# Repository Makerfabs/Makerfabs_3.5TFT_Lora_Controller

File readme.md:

# Makerfas 3.5“ TFT Lora Controller

```c++
/*
Version:		V1.2
Author:			Vincent
Create Date:	2021/9/18
Note:
		V1.1 Add more description.
		V1.2 Add wiki and shop link. Add Lora Kit firmware.
*/
```

[toc]

# Makerfabs

[Makerfabs home page](https://www.makerfabs.com/)

[Makerfabs Wiki](https://wiki.makerfabs.com/)

# Lora Radio Expansion

## Intruduce

Product Link ：[Lora-radio-expansion-for-esp32-display](https://www.makerfabs.com/lora-radio-expansion-for-esp32-display.html)

Wiki Link :  [LoRa_Radio_Expansion](https://wiki.makerfabs.com/MaTouch_3.5_TFT_Touch_with_Camera.html#use-with-lora-radio-expansion)

LoRa Radio expansion based on the LoRa module and provided a wireless Lot solution (ESP32-LoRa). This board is designed for ESP32 3.5" TFT Touch with Camera (also for the 3.2" one), mainly used with the ESP32 3.5" TFT Touch board.

We used LoRa Radio expansion and  ESP32 3.5" TFT Touch with Camera to make a Lora control terminal, which can control multiple Lora devices at the same time through the touch screen and display the device status in real time.

It is an extension of Touch Screen Camera series.

[ESP32 TFT LCD with Camera(3.5'')](https://wiki.makerfabs.com/MaTouch_3.5_TFT_Touch_with_Camera.html))

[ESP32 TFT LCD with Camera(3.2'')](https://wiki.makerfabs.com/MaTouch_3.2_TFT_LCD_with_Camera.html))

## Feature

- Onboard LoRa module (433Mhz, 868Mhz or 915Mhz)
- Long communication distance: 2km or more
- Active buzzer
- Power by 3.3V

### Front:

### Back:

# Makerfas 3.5“ TFT Lora Controller

**Disclaimer, this is only a demo, not as a hardware product for sale, only for reference.**

## Introduce

[ESP32 TFT LCD with Camera(3.5'')](https://wiki.makerfabs.com/MaTouch_3.5_TFT_Touch_with_Camera.html)) was used as a demonstration.

An open Lora control terminal that currently supports 6 Makerfabs of Lora nodes (some are not for sale).  Realizes UI interface, can increase sensor according to UID. And there are different control interfaces for different nodes. 

Five nodes can be online at the same time and the node status is updated periodically. 

## How to use

We're going to post a video to show you how to do that.

### Main page

The main page allows you to add nodes, clear all nodes, and enter receive mode.

The status of each logged node can be updated periodically.

And you can click the node button to enter the node interface.

### Node Page

In node page, you can view the node type, UID, and icon.

You can also refresh the node status periodically.

### Node Control Page

Some types of nodes have control functions, such as controlling the Relay switch and the size of AC Dimmer.

Click the button to enter the keypad or change the switch state.

## Code Upload

Firmware is in .\firmware\ESP32TFT3.5-LORA

### Compiler Options

**If you have any questions，such as how to install the development board, how to download the code, how to install the library. Please refer to :[Makerfabs_FAQ](https://github.com/Makerfabs/Makerfabs_FAQ)**

- Install board : ESP32 (Version 1.0.6)

- Install library: LovyanGFX, RadioLib(Version 4.6.0)

- Copy all bmp file to TF cards and insert to esp32
- Upload codes, select "ESP32 Wrover Module" and "Huge APP"

*Use other version board or library maybe not be able to complied.*

### Change Lora Frequency

Makerfas 3.5“ TFT Lora Controller main code. The default Lora frequency is 434 MHz, you can change these codes:

```c++
//In .\firmware\ESP32TFT3.5-LORA\makerfabs_pin.h

#define FREQUENCY 434.0
#define BANDWIDTH 125.0
#define SPREADING_FACTOR 9
#define CODING_RATE 7
#define OUTPUT_POWER 10
#define PREAMBLE_LEN 8
#define GAIN 0
```

# Example Nodes

We removed the relevant Lora Nodes demo.
Now all based on the example of "328p + lora" has moved to the [Makerfabs_MaLora]( ()https://github.com/Makerfabs/Makerfabs_MaLora) in the project.

# Lora Soil Monitoring & Irrigation Kit

## Introduce

This Kit is based on ESP32 and Lora. The ESP32 3.5 inch display is the console for the system, it receives the Lora message from Lora moisture sensors (support up to 8 sensors in our default firmware) , and send control commands to Lora 4-chnanel MOSFET(2 4-channel MOSFET supported, with totally 8 channels), to control the connected valves open/close, and thus to control the irrigation for multiple points.

Shop Link: [Lora Soil Monitoring & Irrigation Kit](https://www.makerfabs.com/lora-soil-monitoring-irrigation-kit.html)

Please refer to instructables for instructions:

Instructables Link: [Soil-Monitoring-and-Irrigation-With-Lora](https://www.instructables.com/Soil-Monitoring-and-Irrigation-With-Lora/)

Youtube Link: [Soil Monitoring and Irrigation with Lora - How it Works](https://www.youtube.com/watch?v=p6YZIw9I9zE&feature=emb_imp_woyt)

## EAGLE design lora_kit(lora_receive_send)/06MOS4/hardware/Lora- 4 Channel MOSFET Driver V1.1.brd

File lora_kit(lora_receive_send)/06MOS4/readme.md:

Makerfabs Lora Node：Lora- 4 Channel MOSFET Driver
 ==

```
/*
Version:		V1.2
Author:			Vincent
Create Date:	2022/3/24
Note:
				2022/4/2	V1.2: Change feature describes.
				2022/4/2	V1.1: Fix readme bug, fix code pin
*/
```

[toc]

# Makerfabs

[Makerfabs home page](https://www.makerfabs.com/)

[Makerfabs Wiki](https://makerfabs.com/wiki/index.php?title=Main_Page)

# Introduce

4-Channel Lora MOSFET based on the Arduino, users can program it with Arduino IDE, which is very easy especially suit for the none-programmers. There are also guide for users to learn how to create the first IoT project with this board, with which the starters can learn the hardware and programming skill quickly. 

Product Link ：[Lora - 4 Channel MOSFET Driver](https://www.makerfabs.com/index.php?route=journal2/quickview&pid=725)

Wiki Link : 

## Feature

* ATMEL Atmega328P: High Performance, Low Power Atmel®AVR® 8-Bit Microcontroller
* Speed Grade:20Mhz
* Flash:32Kbytes
* RAM: 2KBytes
* EEPROM: 1Kbytes
* Maximum current: 2A
* Input Voltage: 5~27V DC
* Onboard opticalcoupler*4

### Front

 ## Pin OUT

Control relay pins: 

| Atmega328P | MOS  |
| ---------- | ---- |
| D5         | K1   |
| D6         | K2   |
| D9         | K3   |
| D3         | K4   |

# Command

## Lora Node Massage

```c
Type ID: 06
Short name: MOS4
```

## Action

| ACT  | PARAM             | Description          |
| ---- | ----------------- | -------------------- |
| 114  | 000000(not parse) | Querying node status |
| 000  | 000000(not parse) | Close all MOS        |
| 001  | 000000(not parse) | Open all MOS         |
| 002  | 00XXXX            | Set 4 channel MOS    |

### ACT 002

The last four digits of PARAM represent the states of the four MOS.  

The status ranges from 0 to 8:

| Status | 0    | 1     | 2    | 3     | 4    | 5     | 6    | 7     | 8    |
| ------ | ---- | ----- | ---- | ----- | ---- | ----- | ---- | ----- | ---- |
| Power  | 0%   | 12.5% | 25%  | 37.5% | 50%  | 62.5% | 75%  | 87.5% | 100% |

Command example:

```c
ACT = 000 Close
	ID060000ACT000PARAM000000
	//Close all mosfet

ACT = 001 All Open
	ID060000ACT001PARAM000000
	//Open all mosfet, 100% power
    
ACT = 002 Control 
	PARAM = 0000-8888 MOS Status	0,1/8,...,7/8,1
	ID060000ACT002PARAM008010
    //Set mos0 100%; mos1 0%; mos2 12.5%;mos3 0%
```

## Reply

The reply format is as follows:

```c
ID06XXXX[space]REPLY[space]:[space]MOS4[space][Mosfet Status]
    
ID060001 REPLY : MOS4 0801
```

Spaces cannot be omitted.

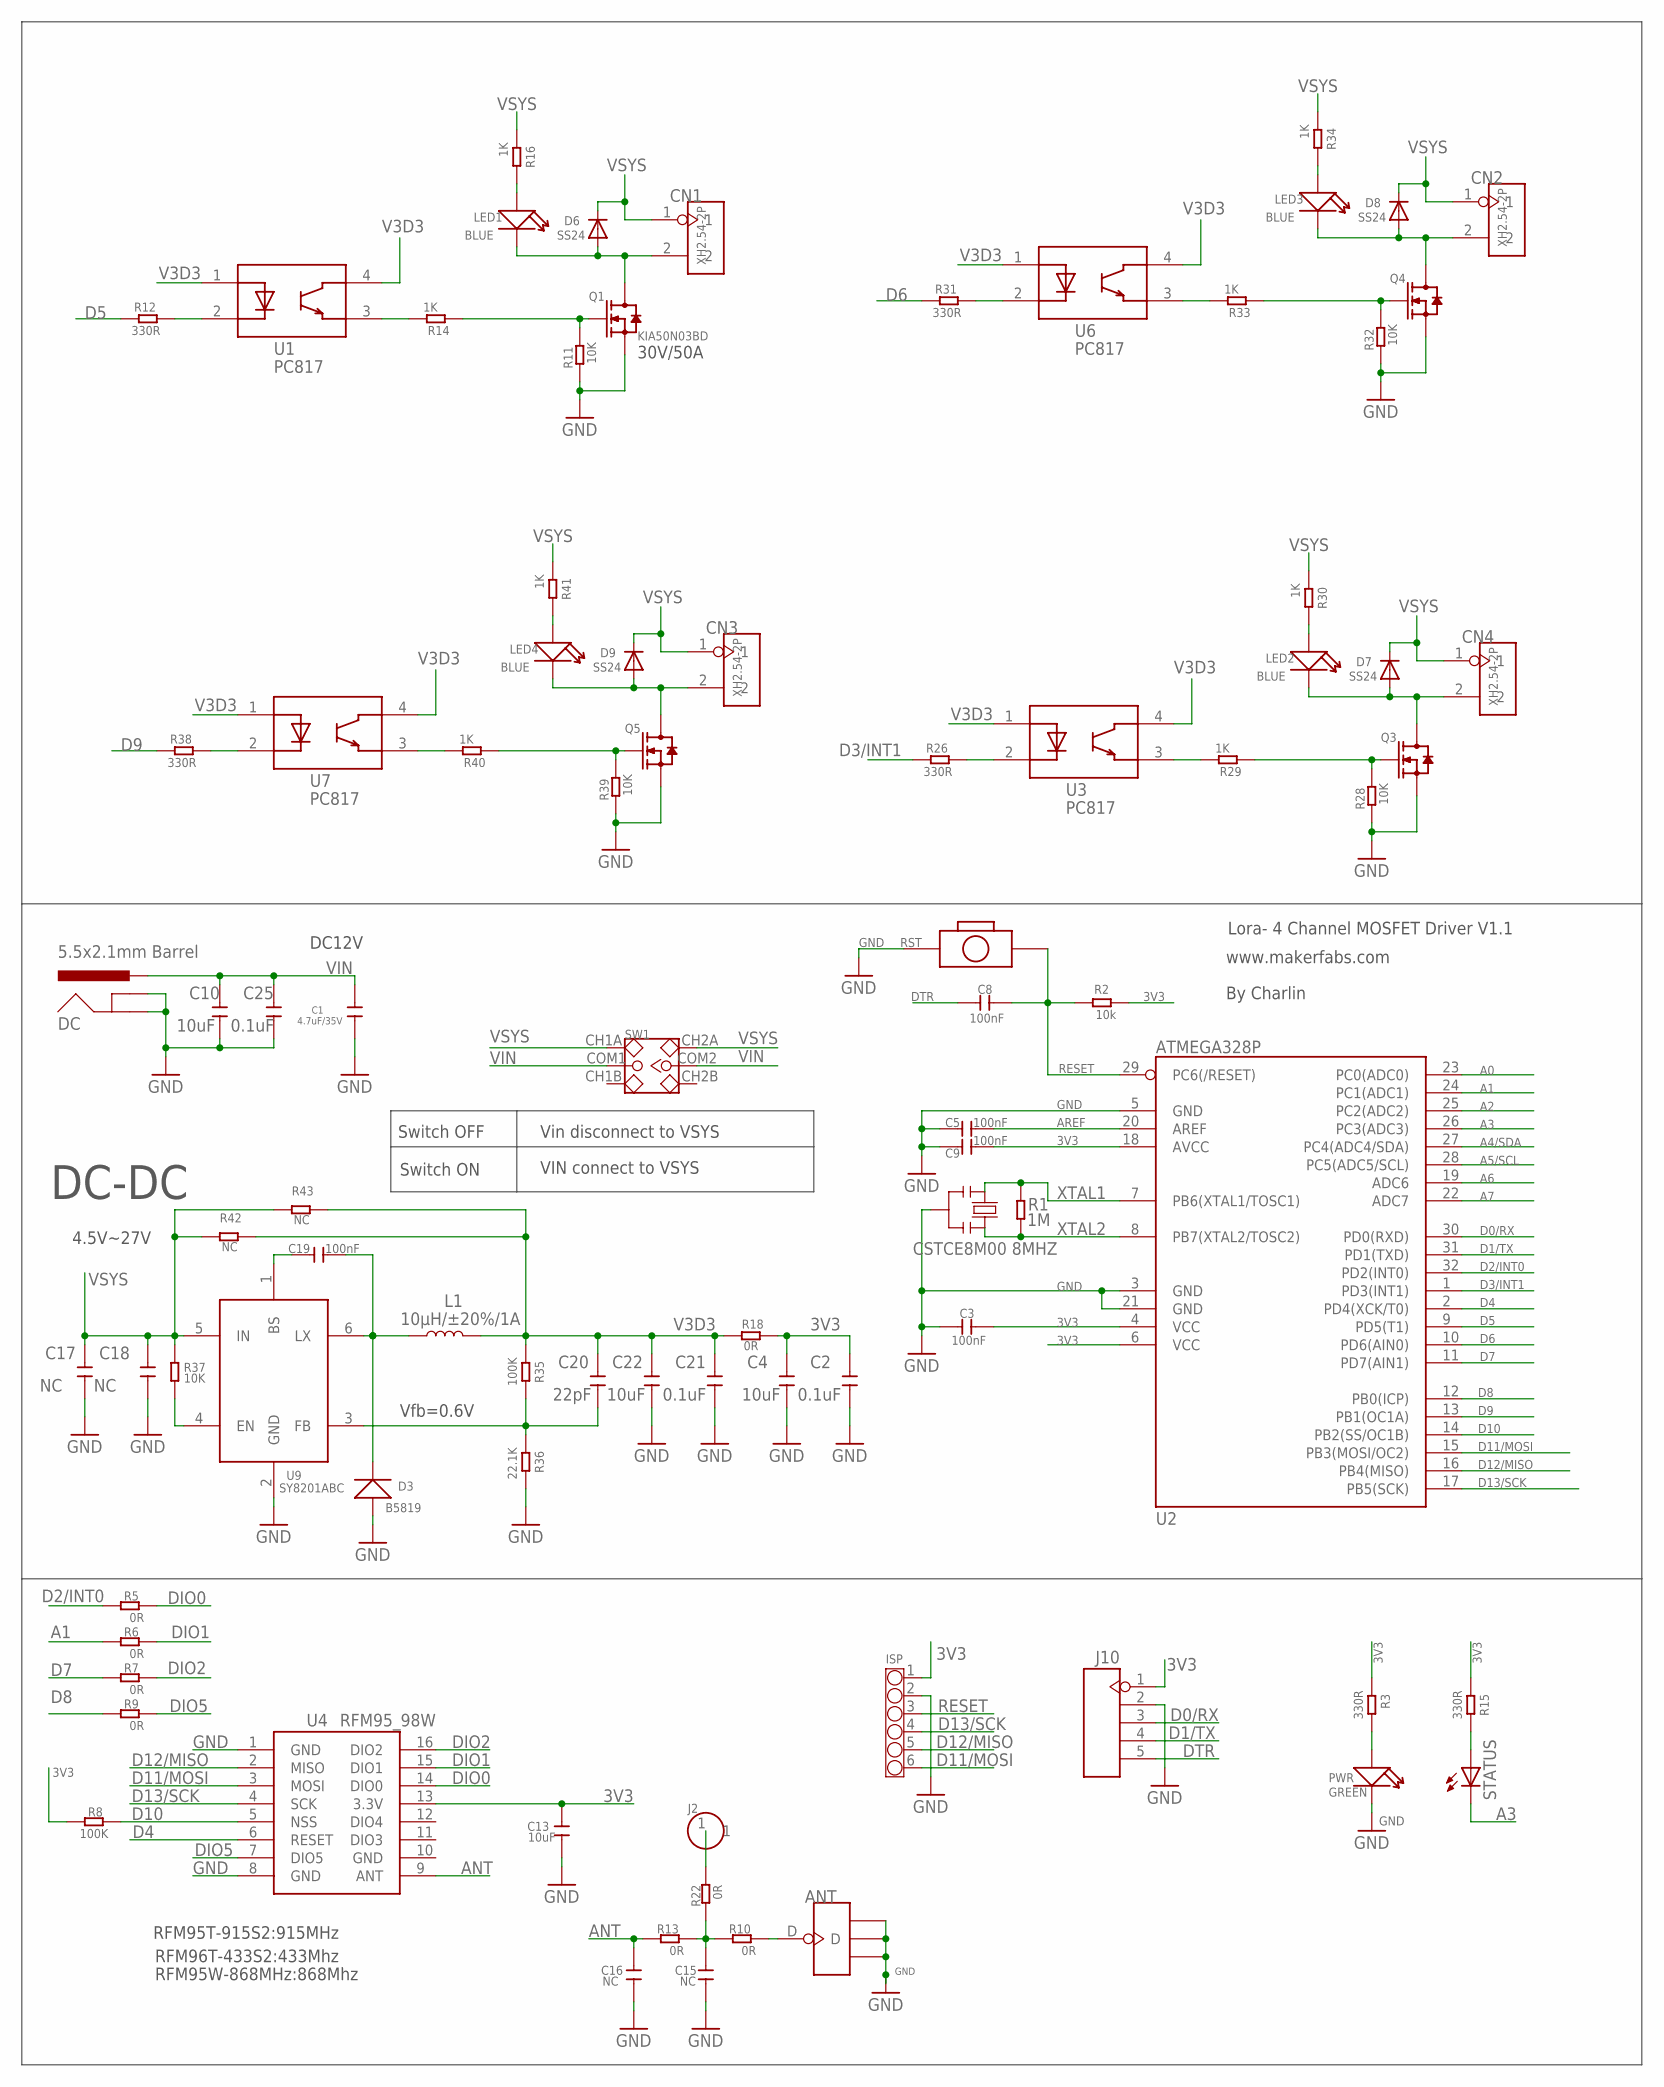
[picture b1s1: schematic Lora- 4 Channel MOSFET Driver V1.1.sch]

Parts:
ANT: ANTENNA-U-FL; 4P-U-FL
C1: 4.7uF/35V; 0603
C2, C21, C25: 0.1uF; 0603
C3, C5, C8, C9, C19: 100nF; 0603
C4, C10, C13, C22: 10uF; 0603
C15, C16, C17, C18: NC; 0603
C20: 22pF; 0603
CN1, CN2, CN3, CN4: XH2.54-2P
D3: B5819; SOD123
D6, D7, D8, D9: SS24; SMADIODE
DC: 5.5x2.1mm Barrel; POWER_JACK_SMD
ISP: CONNECTOR-HEADER-6P-3460270P1; 1X6P-2.54-8.5-BLACK-FEMALE
J2: HEADER-1P-50; 1P-100/50MIL
J10: HEADER-5P-2.54; 5P-2.54
L1: 10µH/±20%/1A; SRN6045
LED1, LED2, LED3, LED4: BLUE; LED-0603
PWR: GREEN; LED-0603
Q1: KIA50N03BD; DISCRETE_TO252
Q3, Q4, Q5: DISCRETE_MOSFET-NP3055LDG; DISCRETE_TO252
R1: 1M; R0603
R2: 10k; R0603
R3, R12, R15, R26, R31, R38: 330R; R0603
R5, R6, R7, R9, R10, R13, R18, R22: 0R; R0603
R8, R35: 100K; R0603
R11, R28, R32, R37, R39: 10K; R0603
R14, R16, R29, R30, R33, R34, R40, R41: 1K; R0603
R36: 22.1K; R0603
R42, R43: NC; R0603
RST: BOTTON-2P-90D; 2P-7.62X3.56-90D
STATUS: LED5MM
SW1: SWITCH-2CH-6P; 6P-2CH-2.54-7.6X3.0
U1, U3, U6, U7: PC817; SMD4-254P-1016L460W
U2: ATMEGA328P; TQFP32
U4: RFM95_98W; RFM92_93W
U9: SY8201ABC; SOT-23-6
Y1: CSTCE8M00 8MHZ; RESONATOR

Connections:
3V3: C2.2, C3.2, C4.2, C9.2, C13.2, ISP.1, J10.1, R2.1, R3.1, R8.2, R15.1, R18.2, U2.4 (VCC), U2.6 (VCC), U2.18 (AVCC), U4.13 (3.3V)
A0: U2.23 (PC0(ADC0))
A1: R6.1, U2.24 (PC1(ADC1))
A2: U2.25 (PC2(ADC2))
A3: STATUS.K (C), U2.26 (PC3(ADC3))
A4/SDA: U2.27 (PC4(ADC4/SDA))
A5/SCL: U2.28 (PC5(ADC5/SCL))
A6: U2.19 (ADC6)
A7: U2.22 (ADC7)
ANT: C16.2, R13.2, U4.9 (ANT)
AREF: C5.2, U2.20 (AREF)
D0/RX: J10.3, U2.30 (PD0(RXD))
D1/TX: J10.4, U2.31 (PD1(TXD))
D2/INT0: R5.1, U2.32 (PD2(INT0))
D3/INT1: R26.1, U2.1 (PD3(INT1))
D4: U2.2 (PD4(XCK/T0)), U4.6 (RESET)
D5: R12.1, U2.9 (PD5(T1))
D6: R31.1, U2.10 (PD6(AIN0))
D7: R7.1, U2.11 (PD7(AIN1))
D8: R9.1, U2.12 (PB0(ICP))
D9: R38.1, U2.13 (PB1(OC1A))
D10: R8.1, U2.14 (PB2(SS/OC1B)), U4.5 (NSS)
D11/MOSI: ISP.6, U2.15 (PB3(MOSI/OC2)), U4.3 (MOSI)
D12/MISO: ISP.5, U2.16 (PB4(MISO)), U4.2 (MISO)
D13/SCK: ISP.4, U2.17 (PB5(SCK)), U4.4 (SCK)
DIO0: R5.2, U4.14 (DIO0)
DIO1: R6.2, U4.15 (DIO1)
DIO2: R7.2, U4.16 (DIO2)
DIO5: R9.2, U4.7 (DIO5)
DTR: C8.1, J10.5
GND: ANT.GND1, ANT.GND2, ANT.GND3, C1.2, C2.1, C3.1, C4.1, C5.1, C9.1, C10.1, C13.1, C15.1, C16.1, C17.1, C18.1, C21.1, C22.1, C25.1, D3.+, DC.GND (GNDBREAK), DC.P$4 (GND), ISP.2, J10.2, PWR.-, Q1.3 (S), Q3.3 (S), Q4.3 (S), Q5.3 (S), R11.1, R28.1, R32.1, R36.2, R39.1, RST.P$1 (1), U2.3 (GND), U2.5 (GND), U2.21 (GND), U4.1 (GND), U4.8 (GND), U4.10 (GND), U9.2 (GND), Y1.2
unnamed: ANT.D, R10.1
unnamed: R12.2, U1.2
unnamed: C15.2, R10.2, R13.1, R22.2
unnamed: R15.2, STATUS.A
unnamed: Q1.1 (G), R11.2, R14.1
unnamed: PWR.+, R3.2
unnamed: J2.1, R22.1
unnamed: CN1.2, D6.A, LED1.-, Q1.2 (D)
unnamed: R14.2, U1.3
unnamed: R26.2, U3.2
unnamed: Q3.1 (G), R28.2, R29.1
unnamed: LED1.+, R16.2
unnamed: R29.2, U3.3
unnamed: CN4.2, D7.A, LED2.-, Q3.2 (D)
unnamed: LED2.+, R30.2
unnamed: R31.2, U6.2
unnamed: C19.2, D3.-, L1.1, U9.6 (LX)
unnamed: C19.1, U9.1 (BS)
unnamed: C20.1, R35.2, R36.1, U9.3 (FB)
unnamed: Q4.1 (G), R32.2, R33.1
unnamed: R33.2, U6.3
unnamed: CN2.2, D8.A, LED3.-, Q4.2 (D)
unnamed: LED3.+, R34.2
unnamed: R38.2, U7.2
unnamed: Q5.1 (G), R39.2, R40.1
unnamed: R40.2, U7.3
unnamed: CN3.2, D9.A, LED4.-, Q5.2 (D)
unnamed: LED4.+, R41.2
unnamed: R37.2, U9.4 (EN)
RESET: C8.2, ISP.3, R2.2, RST.P$2 (2), U2.29 (PC6(/RESET))
V3D3: C20.2, C21.2, C22.2, L1.2, R18.1, R35.1, R42.2, R43.2, U1.1, U1.4, U3.1, U3.4, U6.1, U6.4, U7.1, U7.4
VIN: C1.1, C10.2, C25.2, DC.VIN0 (PWR), SW1.COM1, SW1.COM2
VSYS: C17.2, C18.2, CN1.1, CN2.1, CN3.1, CN4.1, D6.C, D7.C, D8.C, D9.C, R16.1, R30.1, R34.1, R37.1, R41.1, R42.1, R43.1, SW1.CH1A, SW1.CH2A, U9.5 (IN)
XTAL1: R1.2, U2.7 (PB6(XTAL1/TOSC1)), Y1.1
XTAL2: R1.1, U2.8 (PB7(XTAL2/TOSC2)), Y1.3

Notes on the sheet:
RFM95T-915S2:915MHz
RFM96T-433S2:433Mhz
RFM95W-868MHz:868Mhz
Lora- 4 Channel MOSFET Driver V1.1
DC-DC
Switch OFF
Switch ON
Vin disconnect to VSYS
VIN connect to VSYS
DC12V
Vfb=0.6V
4.5V~27V
30V/50A
www.makerfabs.com
By Charlin

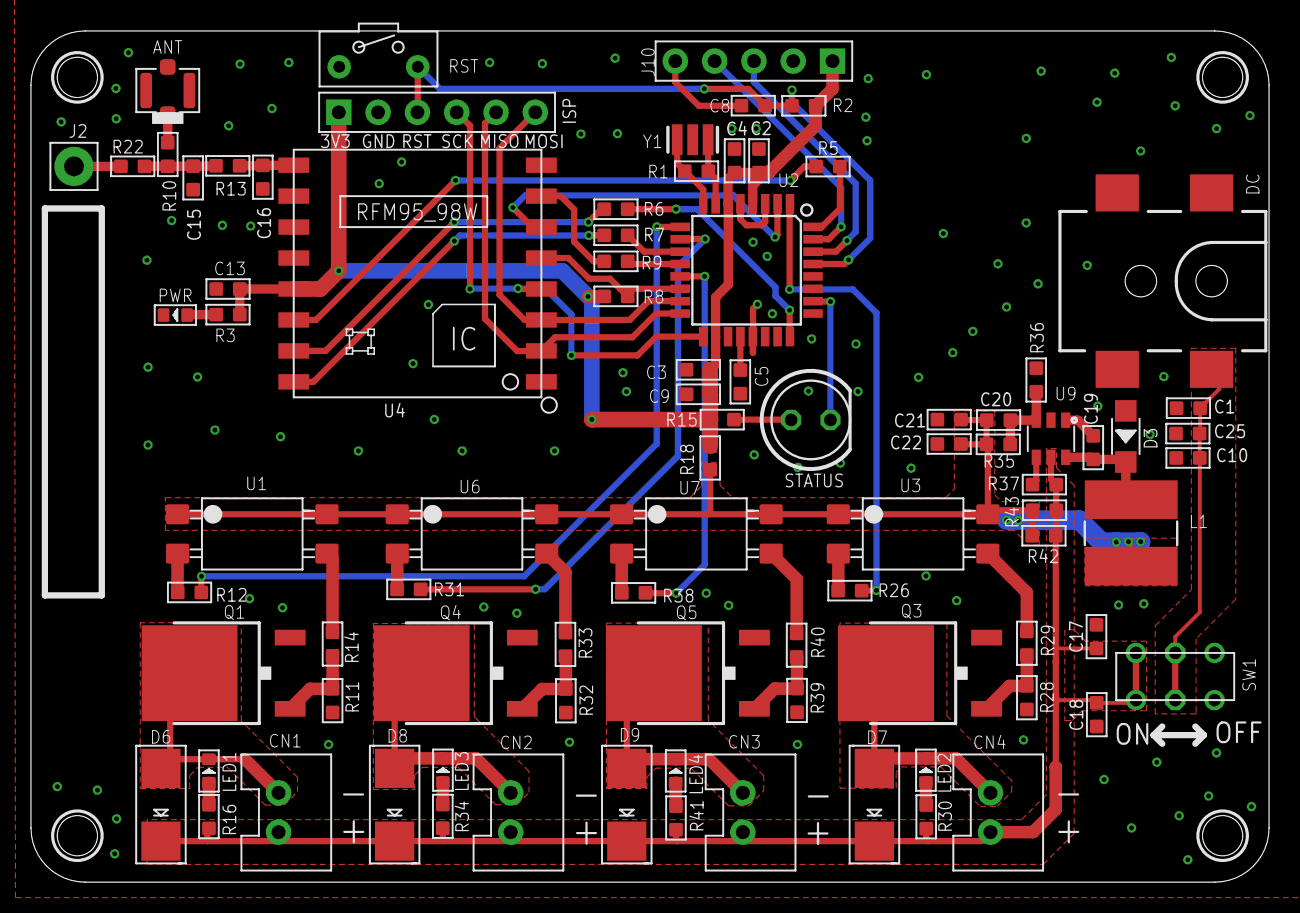
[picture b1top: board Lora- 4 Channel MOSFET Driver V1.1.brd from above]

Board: 2 copper layers, 80.0 x 55.0 mm, 88 parts (1 on the bottom side), 60 nets.

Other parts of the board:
U$1: MAKERFABS_0.3

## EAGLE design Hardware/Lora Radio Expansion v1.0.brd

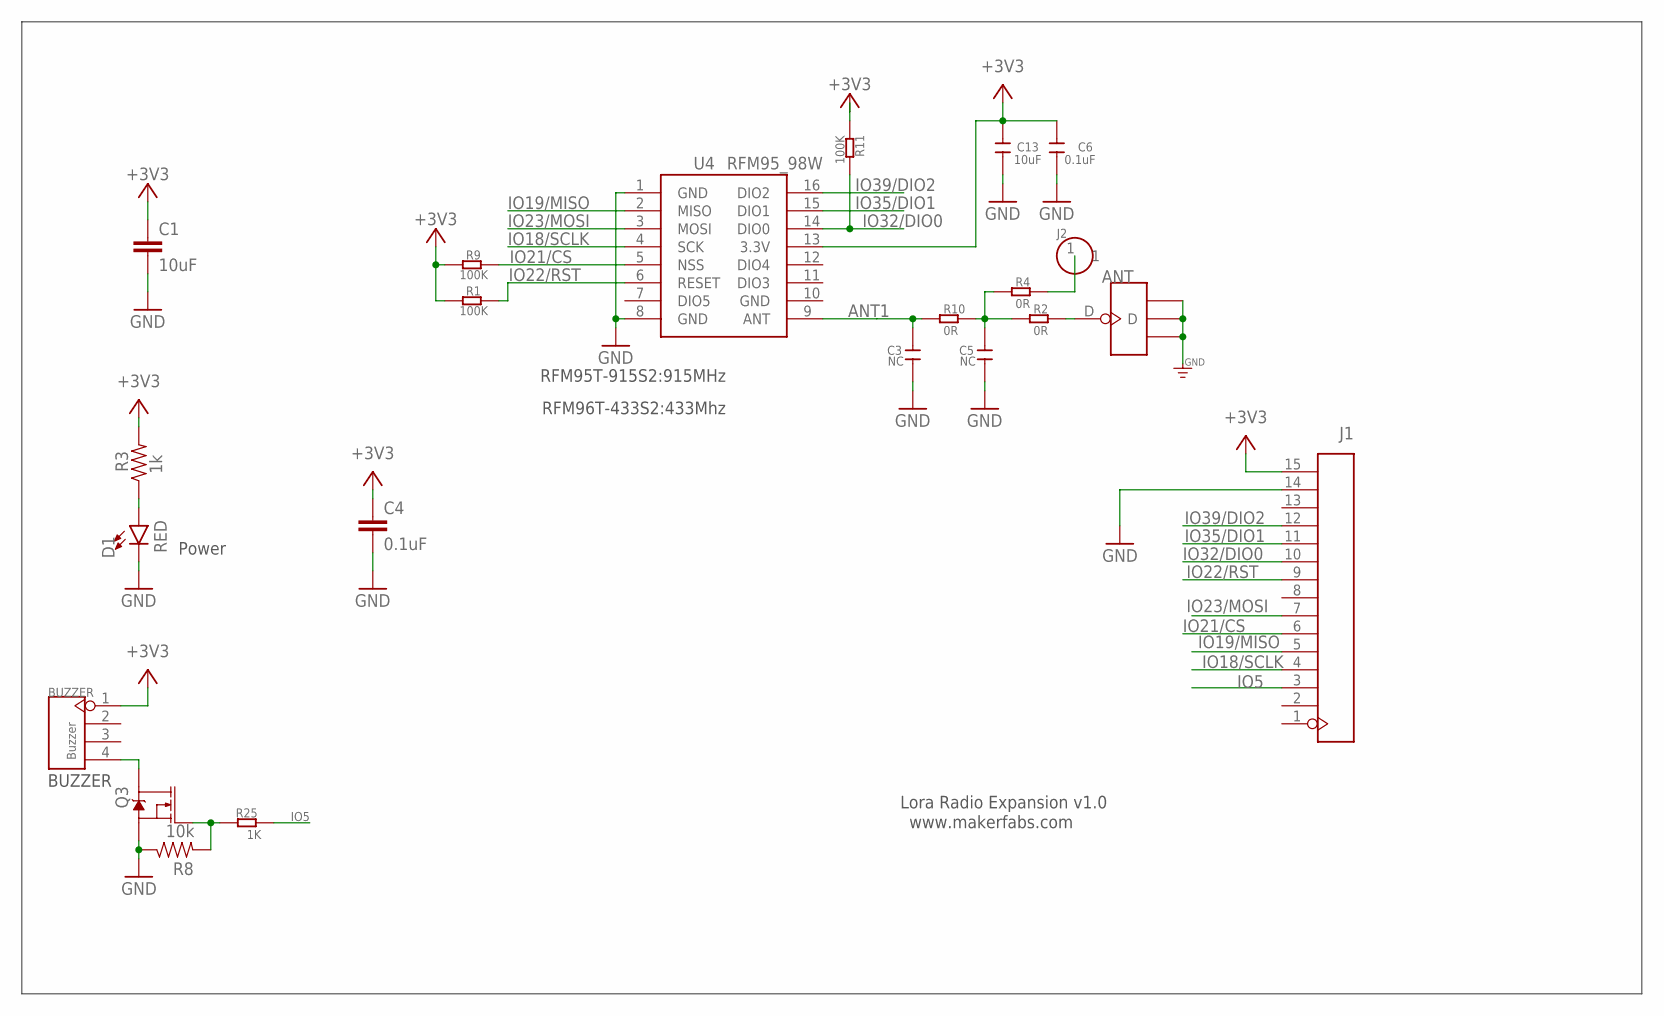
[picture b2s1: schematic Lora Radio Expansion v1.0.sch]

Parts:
ANT: ANTENNA-U-FL; 4P-U-FL
BUZZER: Buzzer; 4P-65/35ROUND
C1, C13: 10uF; 0603
C3, C5: NC; DISCRETE_C0603
C4, C6: 0.1uF; 0603
D1: RED; LED-0603
J1: HEADER-1X15P3; DIP-1X15-2.54MM-W
J2: HEADER-1P-50; 1P-100/50MIL
Q3: 220mA/50V/3.5Ω; SOT23-3
R1, R9, R11: 100K; R0603
R2, R4, R10: 0R; DISCRETE_R0603
R3: 1k; 0603
R8: 10k; 0603
R25: 1K; R0603
U4: RFM95_98W; RFM92_93W

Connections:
+3V3: BUZZER.1, C1.1, C4.1, C6.2, C13.2, J1.15, R1.2, R3.2, R9.2, R11.2, U4.13 (3.3V)
ANT1: C3.2, R10.1, U4.9 (ANT)
GND: ANT.GND1, ANT.GND2, ANT.GND3, C1.2, C3.1, C4.2, C5.1, C6.1, C13.1, D1.C, J1.14, Q3.2 (S), R8.1, U4.1 (GND), U4.8 (GND), U4.10 (GND)
IO5: J1.3, R25.1
IO18/SCLK: J1.4, U4.4 (SCK)
IO19/MISO: J1.5, U4.2 (MISO)
IO21/CS: J1.6, R9.1, U4.5 (NSS)
IO22/RST: J1.9, R1.1, U4.6 (RESET)
IO23/MOSI: J1.7, U4.3 (MOSI)
IO32/DIO0: J1.10, R11.1, U4.14 (DIO0)
IO35/DIO1: J1.11, U4.15 (DIO1)
IO39/DIO2: J1.12, U4.16 (DIO2)
unnamed: BUZZER.4, Q3.3 (D)
unnamed: Q3.1 (G), R8.2, R25.2
unnamed: D1.A, R3.1
unnamed: C5.2, R2.1, R4.1, R10.2
unnamed: ANT.D, R2.2
unnamed: J2.1, R4.2

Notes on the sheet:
Power
Lora Radio Expansion v1.0
www.makerfabs.com
BUZZER
RFM95T-915S2:915MHz
RFM96T-433S2:433Mhz

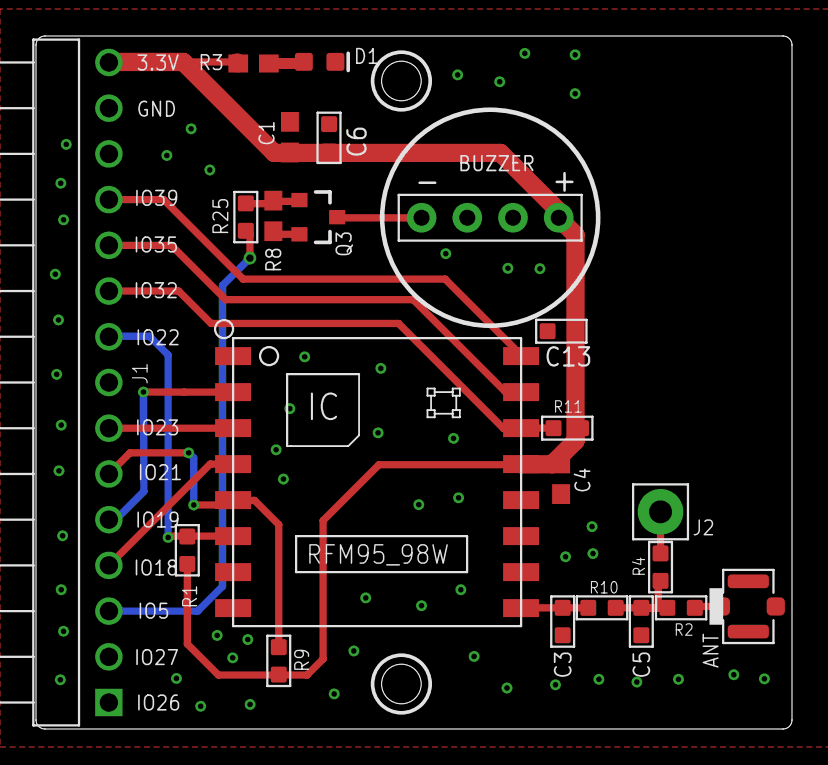
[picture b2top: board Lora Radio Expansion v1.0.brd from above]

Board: 2 copper layers, 42.0 x 38.5 mm, 23 parts (1 on the bottom side), 18 nets.

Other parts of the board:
U$1: MAKERFABS_0.3

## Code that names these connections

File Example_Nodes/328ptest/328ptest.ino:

#include <RadioLib.h>

#define DIO0 2
#define DIO1 6
#define DIO2 7
#define DIO5 8

#define LORA_RST 4
#define LORA_CS 10

#define SPI_MOSI 11
#define SPI_MISO 12
#define SPI_SCK 13

String node_id = String("ID") + "030000";
int id_number_length = 6;
String debug_id = "IDXDEBUG";

/*
Begin method:
Carrier frequency: 434.0 MHz (for SX1276/77/78/79 and RFM96/98) or 915.0 MHz (for SX1272/73 and RFM95/97)
Bandwidth: 125.0 kHz (dual-sideband)
Spreading factor: 9
Coding rate: 4/7
Sync word: SX127X_SYNC_WORD (0x12)
Output power: 10 dBm
Preamble length: 8 symbols
Gain: 0 (automatic gain control enabled)
Other:
Over-current protection: 60 mA
Inaccessible:
LoRa header mode: explicit
Frequency hopping: disabled

*/

#define FREQUENCY 434.0
#define BANDWIDTH 125.0
#define SPREADING_FACTOR 9
#define CODING_RATE 7
#define OUTPUT_POWER 10
#define PREAMBLE_LEN 8
#define GAIN 0

SX1278 radio = new Module(LORA_CS, DIO0, LORA_RST, DIO1);
//SX1278 radio = new Module(LORA_CS, DIO0, LORA_RST, DIO1, SPI, SPISettings());

void setup()
{
    Serial.begin(115200);

    pin_init();

    // initialize SX1278 with default settings
    Serial.print(F("[SX1278] Initializing ... "));

    int state = radio.begin(FREQUENCY, BANDWIDTH, SPREADING_FACTOR, CODING_RATE, SX127X_SYNC_WORD, OUTPUT_POWER, PREAMBLE_LEN, GAIN);

    if (state == ERR_NONE)
    {
        Serial.println(F("success!"));
    }
    else
    {
        Serial.print(F("failed, code "));
        Serial.println(state);
        while (true)
            ;
    }
}

int index = 0;

void loop()
{
    radio.transmit((String) "ID010123 REPLY : SOIL INEDX:" + index + " H:48.85 T:30.50 ADC:896 BAT:1016");
    delay(5000);
}

void loop2()
{
    //Serial.print(F("[SX1278] Waiting for incoming transmission ... "));

    String str;
    int state = radio.receive(str);

    if (state == ERR_NONE)
    {
        // packet was successfully received
        Serial.println(F("success!"));

        // print the data of the packet
        Serial.print(F("[SX1278] Data:\t\t\t"));
        Serial.println(str);

        // print the RSSI (Received Signal Strength Indicator)
        // of the last received packet
        Serial.print(F("[SX1278] RSSI:\t\t\t"));
        Serial.print(radio.getRSSI());
        Serial.println(F(" dBm"));

        // print the SNR (Signal-to-Noise Ratio)
        // of the last received packet
        Serial.print(F("[SX1278] SNR:\t\t\t"));
        Serial.print(radio.getSNR());
        Serial.println(F(" dB"));

        // print frequency error
        // of the last received packet
        Serial.print(F("[SX1278] Frequency error:\t"));
        Serial.print(radio.getFrequencyError());
        Serial.println(F(" Hz"));

        if (command_explain(str))
        {
            String back_str = node_id + " REPLY : RELAY4 " + String("STATUS DATA");
            radio.transmit(back_str);
        }
    }
    else if (state == ERR_RX_TIMEOUT)
    {
        // timeout occurred while waiting for a packet
        //Serial.println(F("timeout!"));
    }
    else if (state == ERR_CRC_MISMATCH)
    {
        // packet was received, but is malformed
        Serial.println(F("CRC error!"));
    }
    else
    {
        // some other error occurred
        Serial.print(F("failed, code "));
        Serial.println(state);
    }
}

void pin_init()
{
}

int command_explain(String str)
{
    //string spilt
    String txt = str;
    if (txt.startsWith(node_id) || txt.startsWith(debug_id))
    {
        //int node_id = (txt.substring(2, 5)).toInt();
        long node_act = txt.substring(id_number_length + 5, id_number_length + 8).toInt();
        int node_param = txt.substring(id_number_length + 14, id_number_length + 20).toInt();

        Serial.println("ACT:  " + String(node_act));
        Serial.println("PARAM: " + String(node_param));

        switch (node_act)
        {
        case 0:
            Serial.println("ALL CLOSE");
            break;

        case 1:
            Serial.println("ALL OPEN");
            break;

        case 2:
            Serial.println("Control");
            //dim = node_param % 1000;
            break;

        case 114:
            Serial.println("CHECK STATUS");
            break;

        default:
            Serial.println("UNKNOWN ACT!");
            return 0;
        }
        return 1;
    }

    return 0;
}

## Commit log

2021-09-07 Create Project
2021-09-09 Update 04TDS
2021-09-15 Add receive mode
2021-09-15 Update TDS to TDV
2021-09-16 Create hardware
2021-09-18 Create expansion receive demo
2021-09-26 Add need picture
2021-09-27 Edit Readme
2022-02-08 Lora_kit demo
2022-02-28 Edit Lora Kit
2022-03-19 RTOS demo
2022-03-22 Finish LoraKitRtos
2022-04-22 Change Button Text
2022-05-11 V1.2 Add lora kit.
2023-08-18 Add demo
2025-05-03 Build/Library updates:
    1. Arduino IDE 1.8
    2. ESP32 by Espessif Systems 3.2.0
    3. RadioLib 7.1.2
    4. LovyanGFX 1.2.7
    Bugs fixed:
    1. Replace hardcoded NTP server IP address with DNS name
2025-05-03 2025 build upgrade
    Build/Library updates:
    1. Arduino IDE 1.8
    2. ESP32 by Espessif Systems 3.2.0
    3. RadioLib 7.1.2
    4. LovyanGFX 1.2.7
    Bugs fixed:
2025-05-27 add lora transmit

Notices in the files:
parts and their libraries:
SparkFun-Capacitors: Licensing: Creative Commons ShareAlike 4.0 International - https://creativecommons.org/licenses/by-sa/4.0
